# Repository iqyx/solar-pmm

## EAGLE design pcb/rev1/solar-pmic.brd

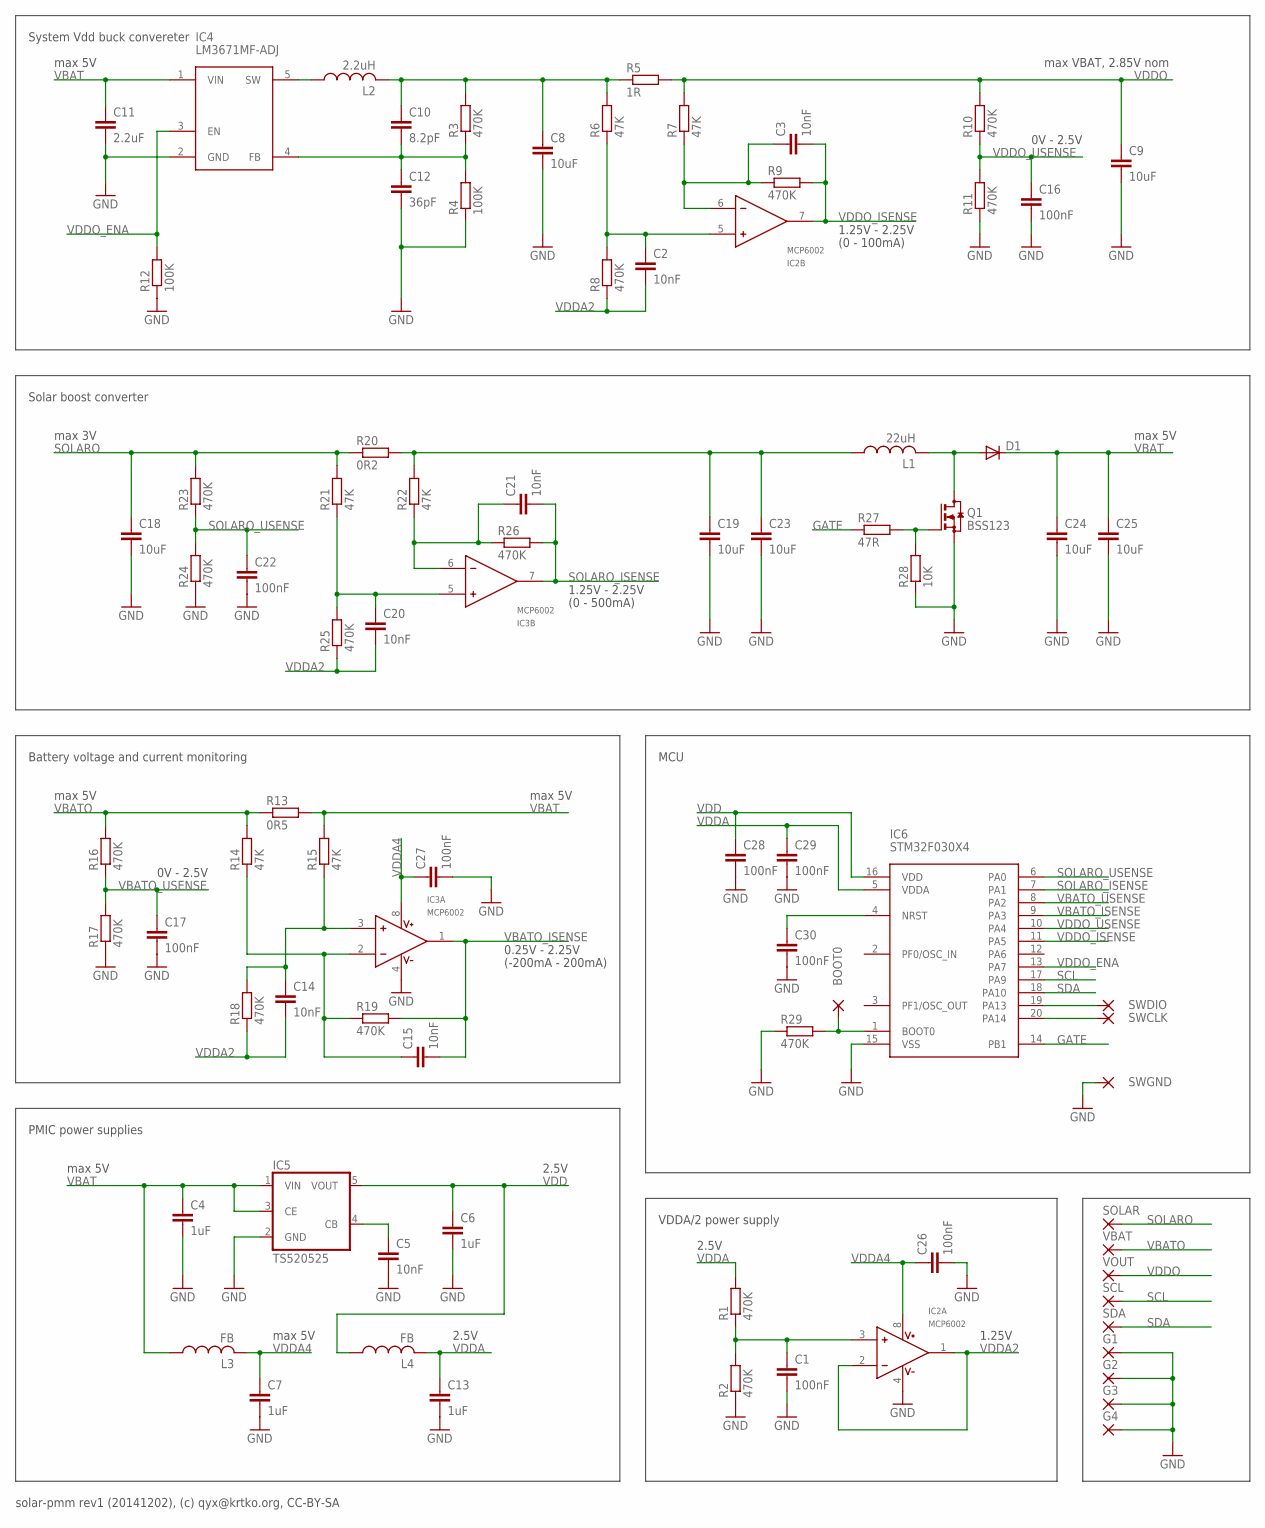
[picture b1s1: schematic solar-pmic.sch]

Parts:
BOOT0: SMD2; SMD1,27-2,54
C1, C16, C17, C22, C26, C27, C28, C29, C30: 100nF; C0603
C2, C3, C5, C14, C15, C20, C21: 10nF; C0603
C4, C6, C7, C13: 1uF; C0603
C8, C9, C18, C19, C23, C24, C25: 10uF; C0805
C10: 8.2pF; C0603
C11: 2.2uF; C0805
C12: 36pF; C0603
D1: DIODE-MINIMELF; MINIMELF
G1, G2, G3, G4: 2,15/1,0
IC2, IC3: MCP6002; MSOP8
IC4: LM3671MF-ADJ; SOT23-5
IC5: TS520525; SOT25
IC6: STM32F030X4; TSSOP20_SO
L1: 22uH; L3225M
L2: 2.2uH; L3225M
L3, L4: FB; L2012C
Q1: BSS123; SOT23
R1, R2, R3, R8, R9, R10, R11, R16, R17, R18, R19, R23, R24, R25, R26, R29: 470K; R0603
R4, R12: 100K; R0603
R5: 1R; R0805
R6, R7, R14, R15, R21, R22: 47K; R0603
R13: 0R5; R0805
R20: 0R2; R0805
R27: 47R; R0603
R28: 10K; R0603
SCL: 2,15/1,0
SDA: 2,15/1,0
SOLAR: 2,15/1,0
SWCLK: SMD2; SMD1,27-2,54
SWDIO: SMD2; SMD1,27-2,54
SWGND: SMD2; SMD1,27-2,54
VBAT: 2,15/1,0
VOUT: 2,15/1,0

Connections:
GATE: IC6.14 (PB1), R27.1
GND: C1.2, C4.2, C5.2, C6.2, C7.2, C8.2, C9.2, C11.2, C12.2, C13.2, C16.2, C17.2, C18.2, C19.2, C22.2, C23.2, C24.2, C25.2, C26.2, C27.2, C28.2, C29.2, C30.2, G1.1, G2.1, G3.1, G4.1, IC2.4 (V-), IC3.4 (V-), IC4.2 (GND), IC5.2 (GND), IC6.15 (VSS), Q1.2 (S), R2.1, R4.1, R11.1, R12.1, R17.1, R24.1, R28.1, R29.1, SWGND.1
unnamed: C1.1, IC2.3 (IN+), R1.1, R2.2
unnamed: C8.1, C10.1, L2.2, R3.2, R5.1, R6.2
unnamed: IC4.5 (SW), L2.1
unnamed: Q1.1 (G), R27.2, R28.2
unnamed: C3.1, IC2.6 (IN-), R7.1, R9.1
unnamed: C2.1, IC2.5 (IN+), R6.1, R8.2
unnamed: C10.2, C12.1, IC4.4 (FB), R3.1, R4.2
unnamed: C21.1, IC3.6 (IN-), R22.1, R26.1
unnamed: C5.1, IC5.4 (CB)
unnamed: C20.1, IC3.5 (IN+), R21.1, R25.2
unnamed: C15.1, IC3.2 (IN-), R14.1, R19.1
unnamed: C19.1, C23.1, L1.1, R20.2, R22.2
unnamed: D1.A, L1.2, Q1.3 (D)
unnamed: C14.1, IC3.3 (IN+), R15.1, R18.2
unnamed: BOOT0.1, IC6.1 (BOOT0), R29.2
unnamed: IC6.19 (PA13), SWDIO.1
unnamed: IC6.20 (PA14), SWCLK.1
unnamed: C30.1, IC6.4 (NRST)
SCL: IC6.17 (PA9), SCL.1
SDA: IC6.18 (PA10), SDA.1
SOLARO: C18.1, R20.1, R21.2, R23.2, SOLAR.1
SOLARO_ISENSE: C21.2, IC3.7 (OUT), IC6.7 (PA1), R26.2
SOLARO_USENSE: C22.1, IC6.6 (PA0), R23.1, R24.2
VBAT: C4.1, C11.1, C24.1, C25.1, D1.C, IC4.1 (VIN), IC5.1 (VIN), IC5.3 (CE), L3.1, R13.2, R15.2
VBATO: R13.1, R14.2, R16.2, VBAT.1
VBATO_ISENSE: C15.2, IC3.1 (OUT), IC6.9 (PA3), R19.2
VBATO_USENSE: C17.1, IC6.8 (PA2), R16.1, R17.2
VDD: C6.1, C28.1, IC5.5 (VOUT), IC6.16 (VDD), L4.1
VDDA: C13.1, C29.1, IC6.5 (VDDA), L4.2, R1.2
VDDA2: C2.2, C14.2, C20.2, IC2.1 (OUT), IC2.2 (IN-), R8.1, R18.1, R25.1
VDDA4: C7.1, C26.1, C27.1, IC2.8 (V+), IC3.8 (V+), L3.2
VDDO: C9.1, R5.2, R7.2, R10.2, VOUT.1
VDDO_ENA: IC4.3 (EN), IC6.13 (PA7), R12.2
VDDO_ISENSE: C3.2, IC2.7 (OUT), IC6.11 (PA5), R9.2
VDDO_USENSE: C16.1, IC6.10 (PA4), R10.1, R11.2

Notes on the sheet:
VDDA/2 power supply
PMIC power supplies
Battery voltage and current monitoring
System Vdd buck convereter
Solar boost converter
max 5V
2.5V
1.25V
max VBAT, 2.85V nom
1.25V - 2.25V
(0 - 100mA)
0V - 2.5V
(0 - 500mA)
0.25V - 2.25V
(-200mA - 200mA)
max 3V
MCU
solar-pmm rev1 (20141202), (c) qyx@krtko.org, CC-BY-SA

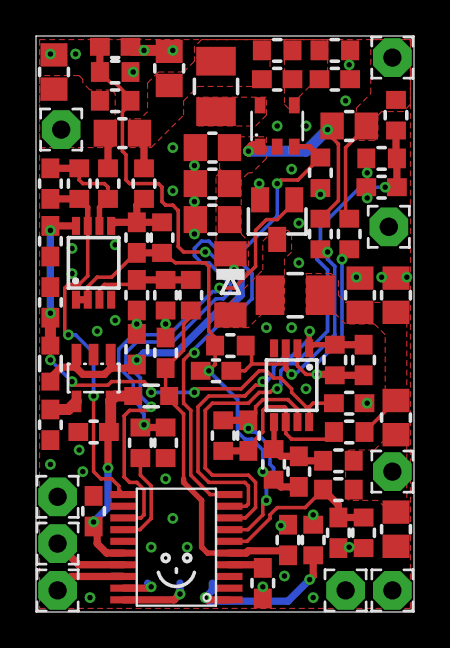
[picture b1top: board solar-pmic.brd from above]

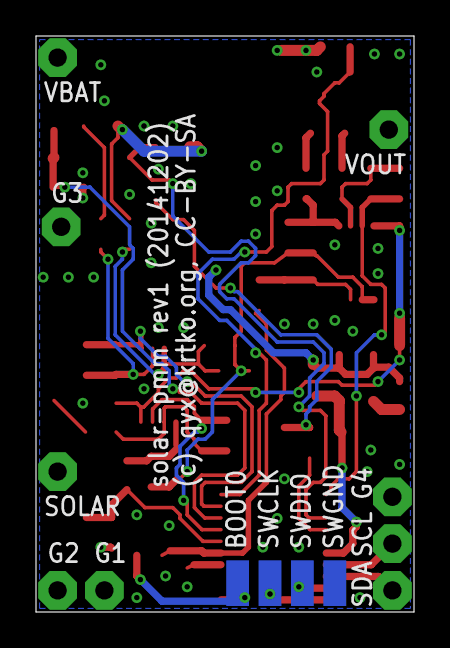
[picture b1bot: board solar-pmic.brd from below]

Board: 2 copper layers, 21.0 x 32.0 mm, 83 parts (4 on the bottom side), 37 nets.

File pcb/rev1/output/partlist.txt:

Partlist

Exported from solar-pmic.sch at 11/25/14 1:19 AM

EAGLE Version 7.1.0 Copyright (c) 1988-2014 CadSoft

Assembly variant: 

Part     Value          Device         Package  Library                 Sheet

C1       100nF          C-EUC0603      C0603    rcl                     1
C2       10nF           C-EUC0603      C0603    rcl                     1
C3       10nF           C-EUC0603      C0603    rcl                     1
C4       1uF            C-EUC0603      C0603    rcl                     1
C5       10nF           C-EUC0603      C0603    rcl                     1
C6       1uF            C-EUC0603      C0603    rcl                     1
C7       1uF            C-EUC0603      C0603    rcl                     1
C8       10uF           C-EUC0805      C0805    rcl                     1
C9       10uF           C-EUC0805      C0805    rcl                     1
C10      8.2pF          C-EUC0603      C0603    rcl                     1
C11      2.2uF          C-EUC0805      C0805    rcl                     1
C12      36pF           C-EUC0603      C0603    rcl                     1
C13      1uF            C-EUC0603      C0603    rcl                     1
C14      10nF           C-EUC0603      C0603    rcl                     1
C15      10nF           C-EUC0603      C0603    rcl                     1
C16      100nF          C-EUC0603      C0603    rcl                     1
C17      100nF          C-EUC0603      C0603    rcl                     1
C18      10uF           C-EUC0805      C0805    rcl                     1
C19      10uF           C-EUC0805      C0805    rcl                     1
C20      10nF           C-EUC0603      C0603    rcl                     1
C21      10nF           C-EUC0603      C0603    rcl                     1
C22      100nF          C-EUC0603      C0603    rcl                     1
C23      10uF           C-EUC0805      C0805    rcl                     1
C24      10uF           C-EUC0805      C0805    rcl                     1
C25      10uF           C-EUC0805      C0805    rcl                     1
C26      100nF          C-EUC0603      C0603    rcl                     1
C27      100nF          C-EUC0603      C0603    rcl                     1
D1                      DIODE-MINIMELF MINIMELF diode                   1
IC2      MCP6002        LT6237CMS8     MSOP8    qyx-misc                1
IC3      MCP6002        LT6237CMS8     MSOP8    qyx-misc                1
IC4      LM3671MF-ADJ   LM3671MF       SOT23-5  qyx-misc                1
IC5      TS520525       TS520525       SOT25    v-reg                   1
L1       22uH           L-USL3225M     L3225M   rcl                     1
L2       2.2uH          L-USL3225M     L3225M   rcl                     1
L3       FB             L-USL2012C     L2012C   rcl                     1
L4       FB             L-USL2012C     L2012C   rcl                     1
PAD1                    2,15/1,0       2,15/1,0 wirepad                 1
PAD2                    2,15/1,0       2,15/1,0 wirepad                 1
PAD3                    2,15/1,0       2,15/1,0 wirepad                 1
PAD4                    2,15/1,0       2,15/1,0 wirepad                 1
PAD5                    2,15/1,0       2,15/1,0 wirepad                 1
PAD6                    2,15/1,0       2,15/1,0 wirepad                 1
PAD7                    2,15/1,0       2,15/1,0 wirepad                 1
PAD8                    2,15/1,0       2,15/1,0 wirepad                 1
PAD9                    2,15/1,0       2,15/1,0 wirepad                 1
Q1       BSS123         BSS123         SOT23    transistor-small-signal 1
R1       470K           R-EU_R0603     R0603    rcl                     1
R2       470K           R-EU_R0603     R0603    rcl                     1
R3       470K           R-EU_R0603     R0603    rcl                     1
R4       100K           R-EU_R0603     R0603    rcl                     1
R5       1R             R-EU_R0805     R0805    rcl                     1
R6       47K            R-EU_R0603     R0603    rcl                     1
R7       47K            R-EU_R0603     R0603    rcl                     1
R8       470K           R-EU_R0603     R0603    rcl                     1
R9       470K           R-EU_R0603     R0603    rcl                     1
R10      470K           R-EU_R0603     R0603    rcl                     1
R11      470K           R-EU_R0603     R0603    rcl                     1
R12      100K           R-EU_R0603     R0603    rcl                     1
R13      0R5            R-EU_R0805     R0805    rcl                     1
R14      47K            R-EU_R0603     R0603    rcl                     1
R15      47K            R-EU_R0603     R0603    rcl                     1
R16      470K           R-EU_R0603     R0603    rcl                     1
R17      470K           R-EU_R0603     R0603    rcl                     1
R18      470K           R-EU_R0603     R0603    rcl                     1
R19      470K           R-EU_R0603     R0603    rcl                     1
R20      0R2            R-EU_R0805     R0805    rcl                     1
R21      47K            R-EU_R0603     R0603    rcl                     1
R22      47K            R-EU_R0603     R0603    rcl                     1
R23      470K           R-EU_R0603     R0603    rcl                     1
R24      470K           R-EU_R0603     R0603    rcl                     1
R25      470K           R-EU_R0603     R0603    rcl                     1
R26      470K           R-EU_R0603     R0603    rcl                     1
R27      47R            R-EU_R0603     R0603    rcl                     1
R28      10K            R-EU_R0603     R0603    rcl                     1

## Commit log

2014-11-25 Initial import.
2014-12-02 Minor schematic fixes + final routing + annotation.
2014-12-02 Add output images (previews).
2014-12-06 Add annotated pcb image.
2014-12-06 Layout changes.
2014-12-06 SeeedStudio rev1.0 gerber output.
2015-01-01 Testing firmware initial import.
    Simple firmware using ChibiOS for testing basic functionality of
    assembled board. All parts are working as intended, further fw
    development needed.
2015-01-01 Add .gitignore files to ignore temporary and build files.
2015-01-05 Change MPPT algo to "incremental conductance".
